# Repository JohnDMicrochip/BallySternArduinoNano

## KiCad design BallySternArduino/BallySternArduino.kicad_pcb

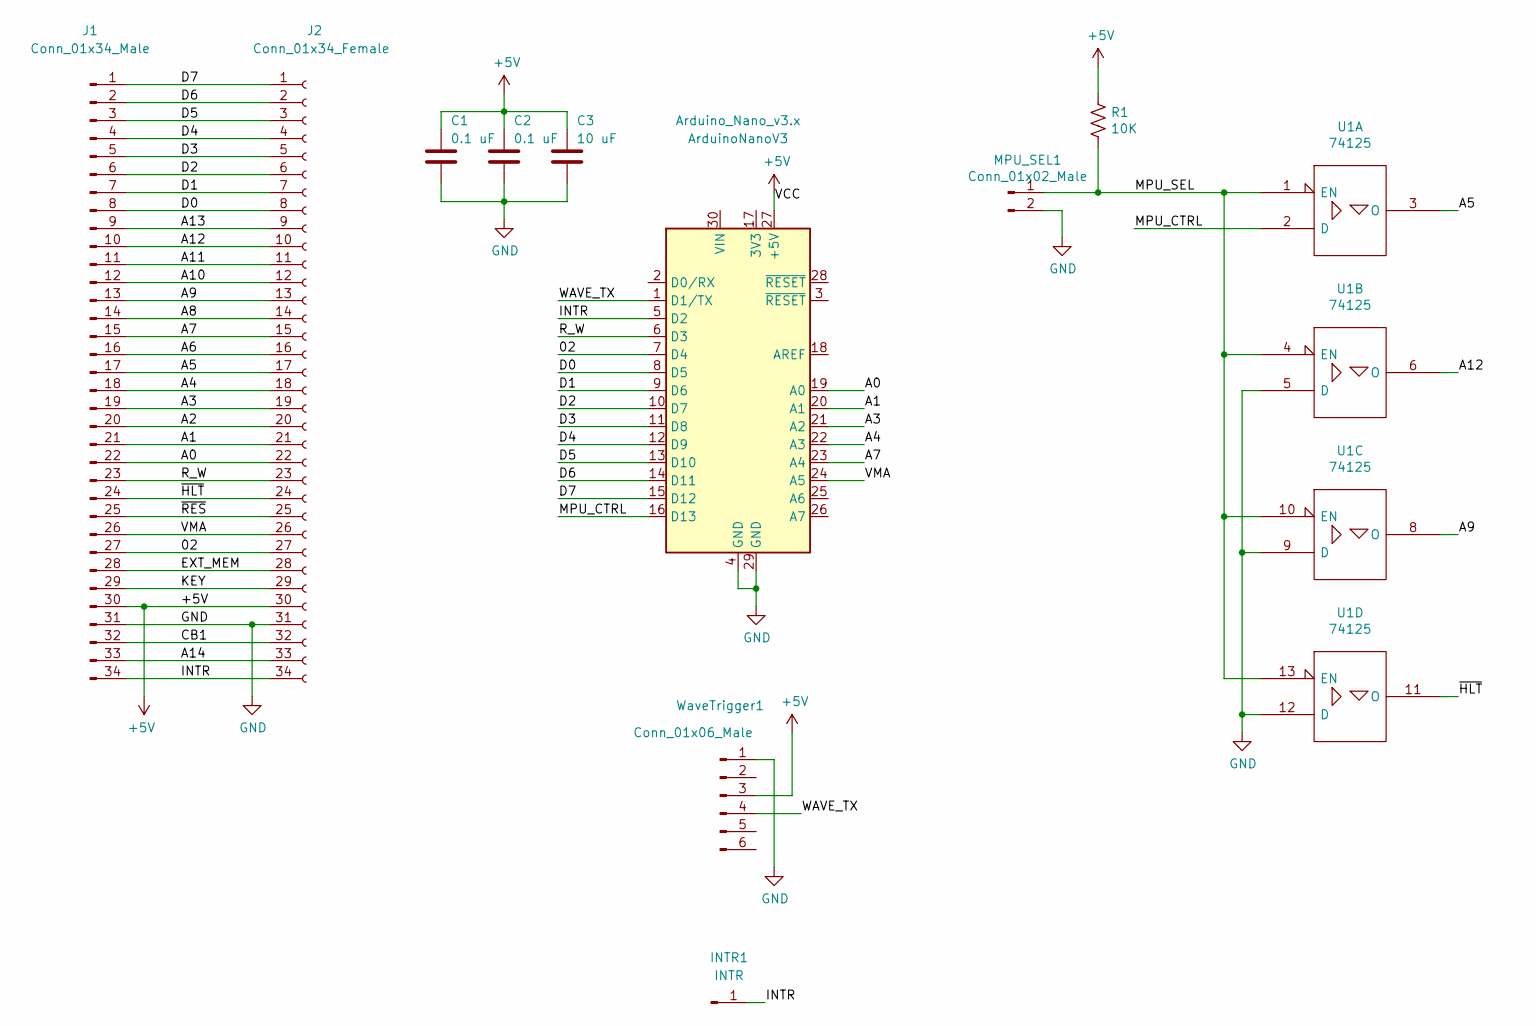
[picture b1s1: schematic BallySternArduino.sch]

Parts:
ArduinoNanoV3: Arduino_Nano_v3.x; Arduino_Nano
C1: 0.1 uF; C_0805_2012Metric_Pad1.15x1.40mm_HandSolder
C2: 0.1 uF; C_Disc_D3.0mm_W2.0mm_P2.50mm
C3: 10 uF; C_0805_2012Metric_Pad1.15x1.40mm_HandSolder
INTR1: INTR; PinHeader_1x01_P2.54mm_Vertical
J1: Conn_01x34_Male; PinHeader_1x34_P2.54mm_Vertical
J2: Conn_01x34_Female; PinSocket_1x34_P2.54mm_Vertical
MPU_SEL1: Conn_01x02_Male; PinHeader_1x02_P2.54mm_Vertical
R1: 10K; R_Axial_DIN0411_L9.9mm_D3.6mm_P15.24mm_Horizontal
U1: 74125; DIP-14_W7.62mm
WaveTrigger1: Conn_01x06_Male; PinHeader_1x06_P2.54mm_Vertical

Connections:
+5V: ArduinoNanoV3.27 (+5V), C1.1, C2.1, C3.1, J1.30, J2.30, R1.1, U1.14 (VCC), WaveTrigger1.3
/02: ArduinoNanoV3.7 (D4), J1.27, J2.27
/A0: ArduinoNanoV3.19 (A0), J1.22, J2.22
/A1: ArduinoNanoV3.20 (A1), J1.21, J2.21
/A2: J1.20, J2.20
/A3: ArduinoNanoV3.21 (A2), J1.19, J2.19
/A4: ArduinoNanoV3.22 (A3), J1.18, J2.18
/A5: J1.17, J2.17, U1.3 (O)
/A6: J1.16, J2.16
/A7: ArduinoNanoV3.23 (A4), J1.15, J2.15
/A8: J1.14, J2.14
/A9: J1.13, J2.13, U1.8 (O)
/A10: J1.12, J2.12
/A11: J1.11, J2.11
/A12: J1.10, J2.10, U1.6 (O)
/A13: J1.9, J2.9
/A14: J1.33, J2.33
/CB1: J1.32, J2.32
/D0: ArduinoNanoV3.8 (D5), J1.8, J2.8
/D1: ArduinoNanoV3.9 (D6), J1.7, J2.7
/D2: ArduinoNanoV3.10 (D7), J1.6, J2.6
/D3: ArduinoNanoV3.11 (D8), J1.5, J2.5
/D4: ArduinoNanoV3.12 (D9), J1.4, J2.4
/D5: ArduinoNanoV3.13 (D10), J1.3, J2.3
/D6: ArduinoNanoV3.14 (D11), J1.2, J2.2
/D7: ArduinoNanoV3.15 (D12), J1.1, J2.1
/EXT_MEM: J1.28, J2.28
/INTR: ArduinoNanoV3.5 (D2), INTR1.1, J1.34, J2.34
/KEY: J1.29, J2.29
/MPU_CTRL: ArduinoNanoV3.16 (D13), U1.2 (D)
/MPU_SEL: MPU_SEL1.1, R1.2, U1.1 (EN), U1.4 (EN), U1.10 (EN), U1.13 (EN)
/R_W: ArduinoNanoV3.6 (D3), J1.23, J2.23
/VMA: ArduinoNanoV3.24 (A5), J1.26, J2.26
/WAVE_TX: ArduinoNanoV3.1 (D1/TX), WaveTrigger1.4
/~HLT: J1.24, J2.24, U1.11 (O)
/~RES: J1.25, J2.25
GND: ArduinoNanoV3.4 (GND), ArduinoNanoV3.29 (GND), C1.2, C2.2, C3.2, J1.31, J2.31, MPU_SEL1.2, U1.5 (D), U1.7 (GND), U1.9 (D), U1.12 (D), WaveTrigger1.1

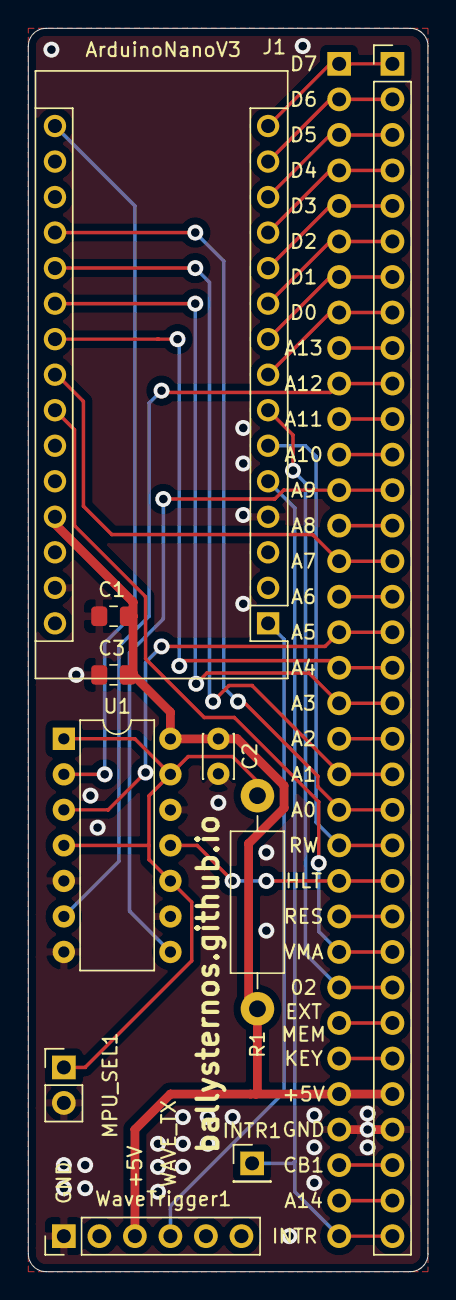
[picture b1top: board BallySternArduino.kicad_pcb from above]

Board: 2 copper layers, 28.6 x 88.9 mm, 11 parts (1 on the bottom side), 37 nets.

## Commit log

2021-04-30 PCB Design Revision A
